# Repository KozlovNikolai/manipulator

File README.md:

<!-- PROJECT LOGO -->
<br />
<div align="center">

<h3 align="center">Проект автоматического телеграфного ключа для тренировки и соревнований по скоростному телеграфированию</h3>

<!-- TABLE OF CONTENTS -->
<details>
  <summary>Содержание</summary>
  <ol>
    <li><a href="#о-проекте">О проекте</a></li>
    <li><a href="#начало">Начало</a></li>
    <li><a href="#лицензия">Лицензия</a></li>
    <li><a href="#контакты">Контакты</a></li>
  </ol>
</details>

<!-- ABOUT THE PROJECT -->
## О проекте

![Product Name Screen Shot][front-img]

<p align="left">
Проект был задуман как ответ на запрос от телеграфистов скоростников на изготовление автоматического ключа, отвещающего следующим требованиям:</p>

* <p align="left">скорость работы ключа не менее 400 СРМ</p>
* <p align="left">поддержка всех режимов работы манипулятора: Iambic A, Iambic AT, Iambic B, Classic</p>
* <p align="left">два выхода управления: реле и оптопара</p>
* <p align="left">звуковая индикация</p>
* <p align="left">индикация заряда батареи</p>
* <p align="left">режим тренировки/контест</p>
* <p align="left">вывод в текстовый редактор на компьютер набираемых символов (как будто их набирают на клавиатуре)</p>
* <p align="left">отображение всех настроек и режимов на дисплее</p>
* <p align="left">сохранение текущих настроек в энергонезависимую память</p>

Текущая версия = 4.32

<p align="right">(<a href="#readme-top">back to top</a>)</p>

<!-- GETTING STARTED -->
## Начало

Для установки программы требуются:

* Arduino IDE
* Микроконтроллер AtMega32u4

После прошивки требуется вставить контроллер в манипулятор, изготовленный в соответствии с <a href="https://github.com/KozlovNikolai/manipulator/tree/master/manipulyator">проектом</a>.

<p align="right">(<a href="#readme-top">back to top</a>)</p>

<!-- LICENSE -->
## Лицензия

Распостраняется свободно.

<p align="right">(<a href="#readme-top">back to top</a>)</p>

<!-- CONTACT -->
## Контакты

Николай Козлов:\
Telegram: @gremiha3\
e-mail: gremiha3@yandex.ru

Project Link: [https://github.com/KozlovNikolai/manipulator](https://github.com/KozlovNikolai/manipulator)

<p align="right">(<a href="#readme-top">back to top</a>)</p>

<!-- MARKDOWN LINKS & IMAGES -->
<!-- https://www.markdownguide.org/basic-syntax/#reference-style-links -->
[arduino-img]: https://cdn.arduino.cc/header-footer/prod/assets/headerLogo-arduino.svg
[arduino-link]: https://www.arduino.cc/
[front-img]: фото/front.jpg

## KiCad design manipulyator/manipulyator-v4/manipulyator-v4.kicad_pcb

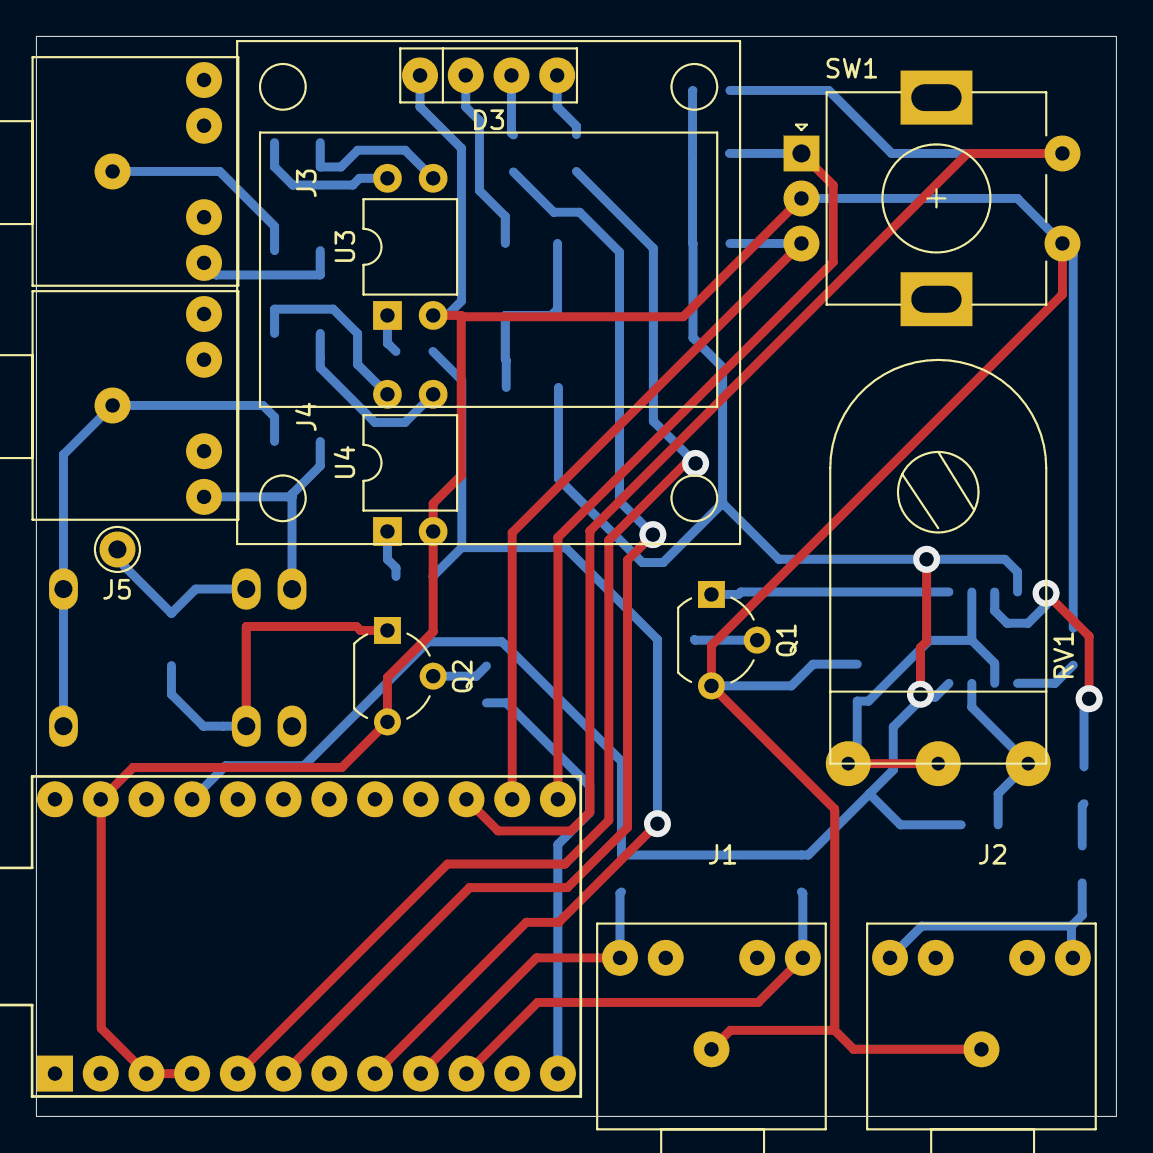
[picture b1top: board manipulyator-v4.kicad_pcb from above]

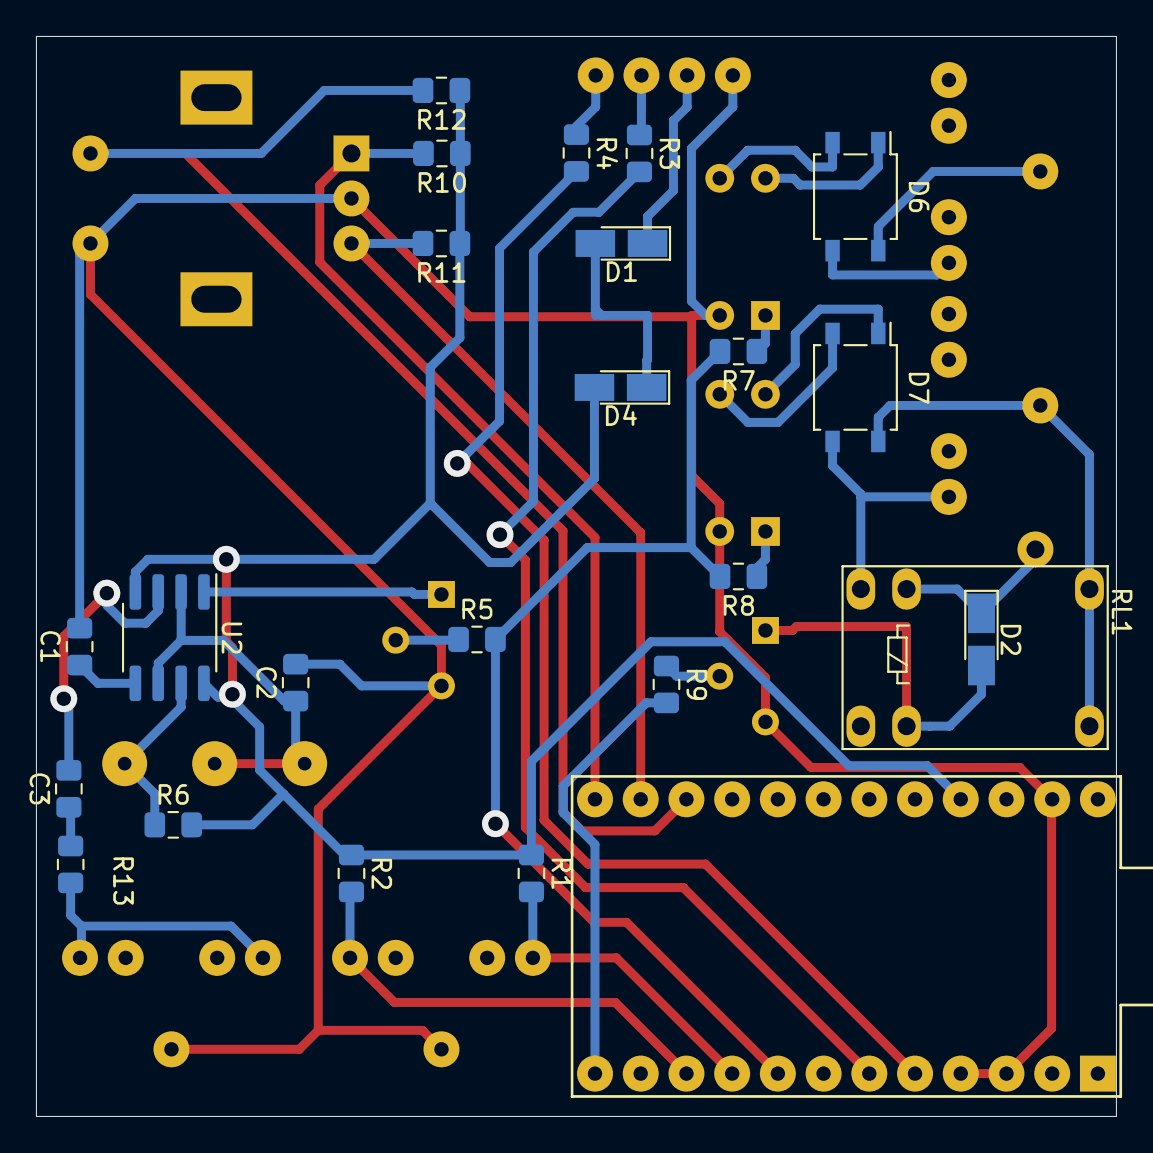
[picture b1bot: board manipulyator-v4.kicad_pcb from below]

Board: 2 copper layers, 60.0 x 60.0 mm, 36 parts (23 on the bottom side), 36 nets.

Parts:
C1: 0.01; C_0805_2012Metric_Pad1.15x1.40mm_HandSolder
C2, C3: 0.1; C_0805_2012Metric_Pad1.15x1.40mm_HandSolder
D1, D2, D4: 1N4148; D_MicroMELF_Hadsoldering
D3: oled_128x64_i2c_ssd1306
D6, D7: D_Bridge_+-AA; SO-4_4.4x4.3mm_P2.54mm
J1, J2, J3, J4: AudioJack2_Ground_Switch; audio-3.5mm-5pin
J5: Conn_01x01; Pin_D1.0mm_L10.0mm
Q1, Q2: BC547; TO-92_Wide
R1, R2, R5, R9: 4k7; R_0805_2012Metric_Pad1.15x1.40mm_HandSolder
R3, R4, R13: 100; R_0805_2012Metric_Pad1.15x1.40mm_HandSolder
R6, R10, R11, R12: 10k; R_0805_2012Metric_Pad1.15x1.40mm_HandSolder
R7, R8: 510; R_0805_2012Metric_Pad1.15x1.40mm_HandSolder
RL1: JRC-21F_4100; Relay_SPDT_HJR-4102
RV1: 10k; perem_resistor-step-5mm
SW1: Rotary_Encoder_Switch; RotaryEncoder_Alps_EC11E-Switch_Vertical_H20mm
U1: ProMicro
U2: NE555; SOP-8_3.76x4.96mm_P1.27mm
U3, U4: PC817; DIP-4_W7.62mm

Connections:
+5V: D4.2, R1.1, R2.1, R6.2, R10.1, R11.1, R12.1, U1.21, U2.4, U2.8
GND: C1.2, C2.2, D3.1, J1.G, J2.G, Q1.3, Q2.3, SW1.C, SW1.S1, U1.3, U1.4, U1.23, U3.2, U4.2
unnamed: C1.1, U2.5
unnamed: C2.1, RV1.1, RV1.2, U2.2, U2.6
unnamed: C3.1, R13.2
unnamed: C3.2, U2.3
unnamed: D1.1, D3.2
unnamed: D1.2, D4.1
unnamed: D2.1, J5.1, RL1.5
unnamed: D2.2, Q2.1, RL1.8
unnamed: D3.3, R3.1
unnamed: D3.4, R4.1
unnamed: D6.1, U3.4
unnamed: D6.2, U3.3
unnamed: D6.3, J3.T
unnamed: D6.4, J3.G
unnamed: D7.1, U4.4
unnamed: D7.2, U4.3
unnamed: D7.3, J4.T, RL1.6
unnamed: D7.4, J4.G, RL1.1, RL1.12
unnamed: J1.S, R1.2, U1.9
unnamed: J1.T, R2.2, U1.10
unnamed: J2.S, J2.T, R13.1
unnamed: Q1.1, U2.1
unnamed: Q1.2, R5.1
unnamed: Q2.2, R9.1
unnamed: R3.2, U1.6
unnamed: R4.2, U1.5
unnamed: R5.2, R7.2, R8.2, U1.8
unnamed: R6.1, RV1.3, U2.7
unnamed: R7.1, U3.1
unnamed: R8.1, U4.1
unnamed: R9.2, U1.12
unnamed: R10.2, SW1.A, U1.13
unnamed: R11.2, SW1.B, U1.14
unnamed: R12.2, SW1.S2, U1.15

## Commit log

2024-05-16 push to git
2024-05-16 add readme template
2024-05-16 add pcb
2024-05-16 finish readme
2024-05-17 set latest version 4.32
